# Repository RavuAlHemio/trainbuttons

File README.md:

# trainbuttons

Two boards providing buttons for controlling a train (simulator).

The buttons are provided by keyboard key switches (Cherry MX or compatible). The two boards are to be interconnected via a repurposed HDMI cable; the left board is then connected via USB-C to the computer.

The button layout is inspired by the results of the EUDDplus (European Driver's Desk plus) project and UIC 612. The icons are reconstructed from those in EN 16186-2. The buttons chosen are those supported, or expected to be supported, by the Zusi simulator.

The design does not include throttle or brake levers; potentiometer-based solutions are available from [Stillertec](https://fahrpult.com/).

The default firmware lets the device appear as a HID gamepad device with zero axes and 21 buttons. A debug pin header is provided on the board to allow installation of other firmware.

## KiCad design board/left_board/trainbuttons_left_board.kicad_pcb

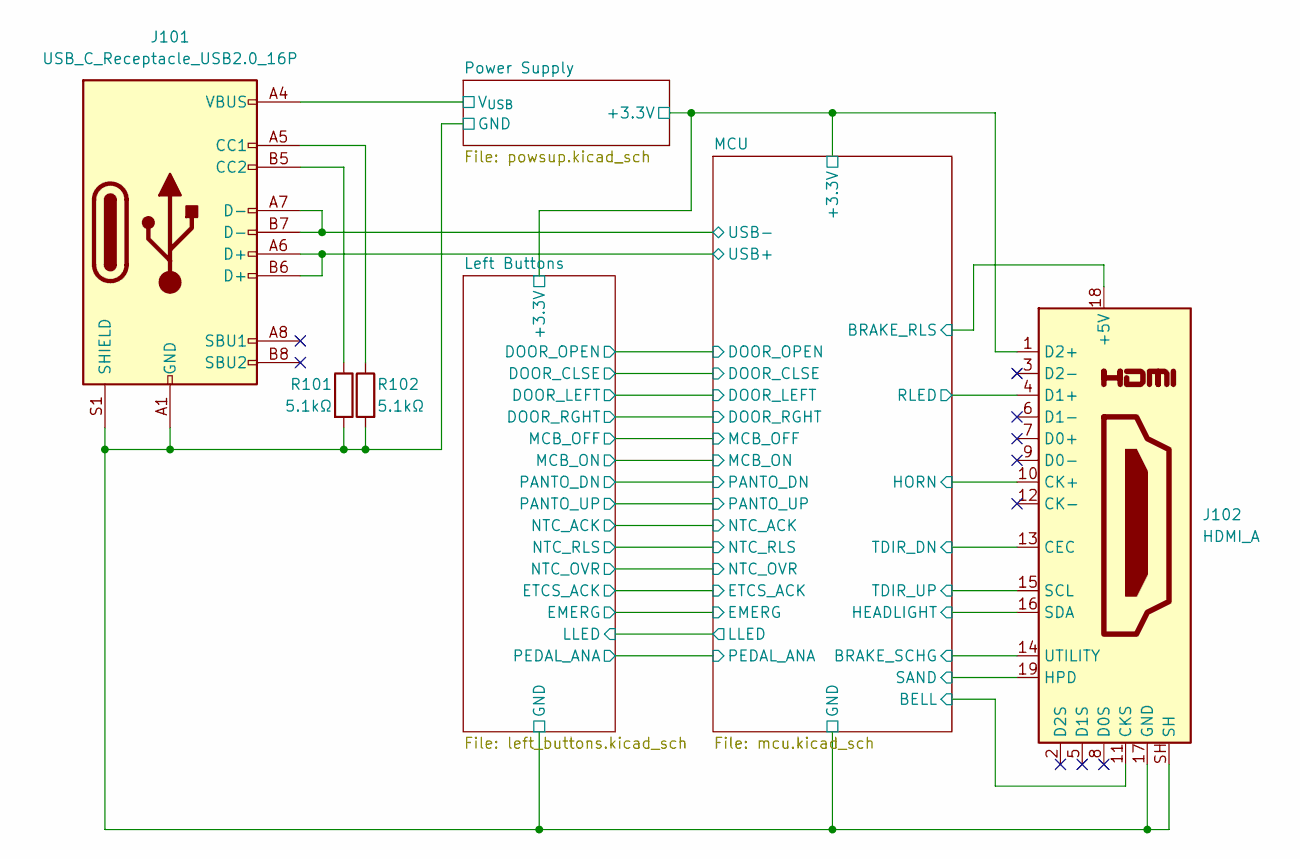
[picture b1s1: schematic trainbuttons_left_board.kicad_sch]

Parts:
J101: USB_C_Receptacle_USB2.0_16P; USB_C_Receptacle_G-Switch_GT-USB-7010ASV; LCSC C2988369
J102: HDMI_A; HDMI_A_Molex_208658-1001_Horizontal; LCSC C2858275
R101, R102: 5.1kΩ; R_0402_1005Metric; LCSC C25905

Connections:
/Left Buttons/+3.3V: J102.1 (D2+); also elsewhere on the board
/Left Buttons/GND: J101.A1 (GND), J101.A12 (GND), J101.B1 (GND), J101.B12 (GND), J101.S1 (SHIELD), J102.17 (GND), J102.SH, R101.2, R102.2; also elsewhere on the board
/MCU/BELL: J102.11 (CKS); also elsewhere on the board
/MCU/BRAKE_RLS: J102.18 (+5V); also elsewhere on the board
/MCU/BRAKE_SCHG: J102.14 (UTILITY); also elsewhere on the board
/MCU/HEADLIGHT: J102.16 (SDA); also elsewhere on the board
/MCU/HORN: J102.10 (CK+); also elsewhere on the board
/MCU/RLED: J102.4 (D1+); also elsewhere on the board
/MCU/SAND: J102.19 (HPD); also elsewhere on the board
/MCU/TDIR_DN: J102.13 (CEC); also elsewhere on the board
/MCU/TDIR_UP: J102.15 (SCL); also elsewhere on the board
/MCU/USB+: J101.A6 (D+), J101.B6 (D+); also elsewhere on the board
/MCU/USB-: J101.A7 (D-), J101.B7 (D-); also elsewhere on the board
/Power Supply/V_{USB}: J101.A4 (VBUS), J101.A9 (VBUS), J101.B4 (VBUS), J101.B9 (VBUS); also elsewhere on the board
unnamed: J101.A5 (CC1), R102.1
unnamed: J101.B5 (CC2), R101.1

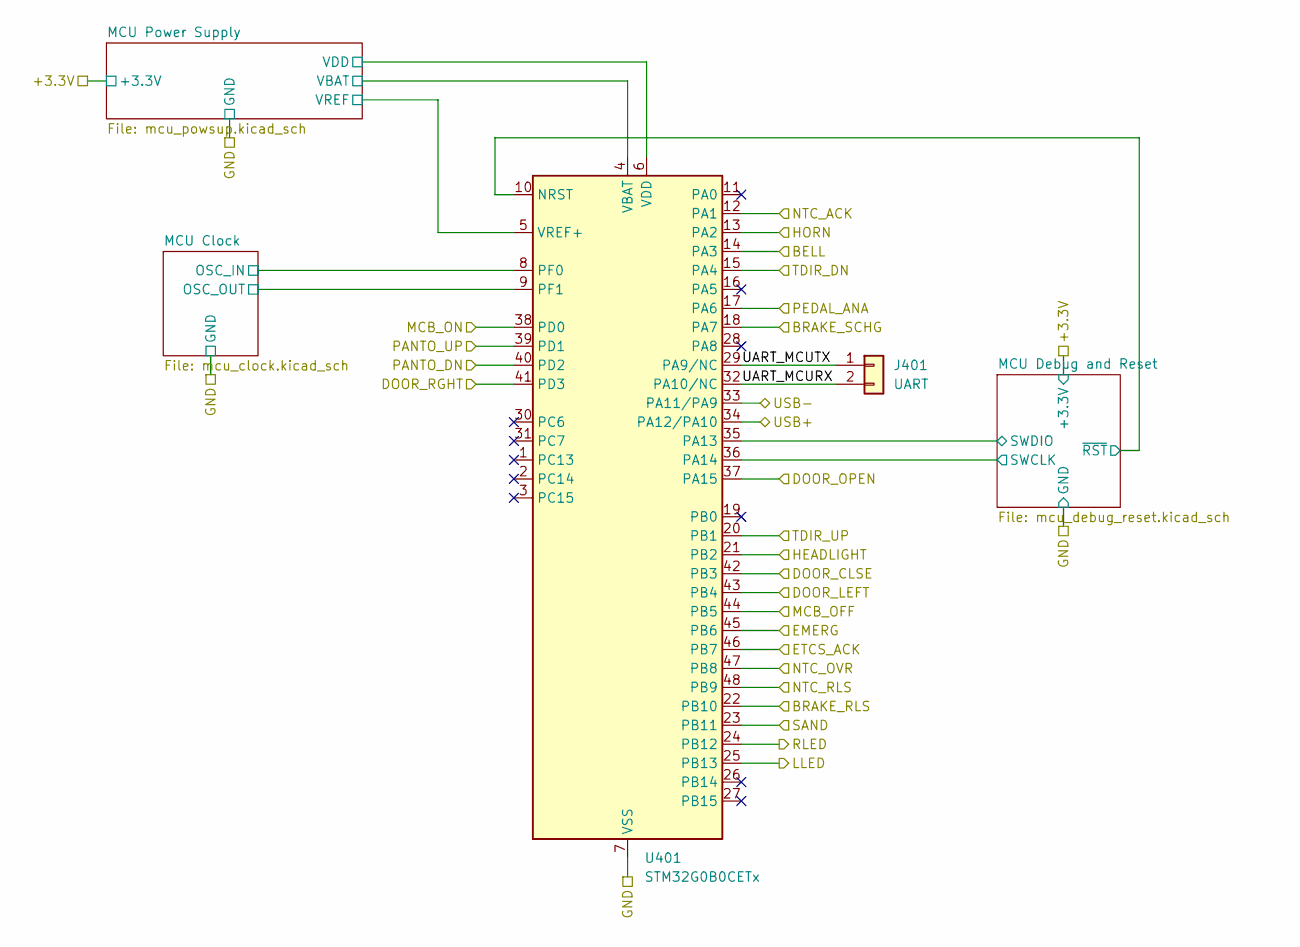
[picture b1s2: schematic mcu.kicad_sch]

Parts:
J401: UART; PinHeader_1x02_P2.54mm_Vertical_SMD_Pin1Left; LCSC C5160785
U401: STM32G0B0CETx; LQFP-48_7x7mm_P0.5mm; LCSC C2826978

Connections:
/Left Buttons/+3.3V: U401.4 (VBAT), U401.6 (VDD); also elsewhere on the board
/Left Buttons/DOOR_CLSE: U401.42 (PB3); also elsewhere on the board
/Left Buttons/DOOR_LEFT: U401.43 (PB4); also elsewhere on the board
/Left Buttons/DOOR_OPEN: U401.37 (PA15); also elsewhere on the board
/Left Buttons/DOOR_RGHT: U401.41 (PD3); also elsewhere on the board
/Left Buttons/EMERG: U401.45 (PB6); also elsewhere on the board
/Left Buttons/ETCS_ACK: U401.46 (PB7); also elsewhere on the board
/Left Buttons/GND: U401.7 (VSS); also elsewhere on the board
/Left Buttons/LLED: U401.25 (PB13); also elsewhere on the board
/Left Buttons/MCB_OFF: U401.44 (PB5); also elsewhere on the board
/Left Buttons/MCB_ON: U401.38 (PD0); also elsewhere on the board
/Left Buttons/NTC_ACK: U401.12 (PA1); also elsewhere on the board
/Left Buttons/NTC_OVR: U401.47 (PB8); also elsewhere on the board
/Left Buttons/NTC_RLS: U401.48 (PB9); also elsewhere on the board
/Left Buttons/PANTO_DN: U401.40 (PD2); also elsewhere on the board
/Left Buttons/PANTO_UP: U401.39 (PD1); also elsewhere on the board
/Left Buttons/PEDAL_ANA: U401.17 (PA6); also elsewhere on the board
/MCU/BELL: U401.14 (PA3); also elsewhere on the board
/MCU/BRAKE_RLS: U401.22 (PB10); also elsewhere on the board
/MCU/BRAKE_SCHG: U401.18 (PA7); also elsewhere on the board
/MCU/HEADLIGHT: U401.21 (PB2); also elsewhere on the board
/MCU/HORN: U401.13 (PA2); also elsewhere on the board
/MCU/MCU Clock/OSC_IN: U401.8 (PF0); also elsewhere on the board
/MCU/MCU Clock/OSC_OUT: U401.9 (PF1); also elsewhere on the board
/MCU/MCU Debug and Reset/SWCLK: U401.36 (PA14); also elsewhere on the board
/MCU/MCU Debug and Reset/SWDIO: U401.35 (PA13); also elsewhere on the board
/MCU/MCU Debug and Reset/~RST: U401.10 (NRST); also elsewhere on the board
/MCU/MCU Power Supply/VREF: U401.5 (VREF+); also elsewhere on the board
/MCU/RLED: U401.24 (PB12); also elsewhere on the board
/MCU/SAND: U401.23 (PB11); also elsewhere on the board
/MCU/TDIR_DN: U401.15 (PA4); also elsewhere on the board
/MCU/TDIR_UP: U401.20 (PB1); also elsewhere on the board
/MCU/UART_MCURX: J401.2, U401.32 (PA10/NC)
/MCU/UART_MCUTX: J401.1, U401.29 (PA9/NC)
/MCU/USB+: U401.34 (PA12/PA10); also elsewhere on the board
/MCU/USB-: U401.33 (PA11/PA9); also elsewhere on the board

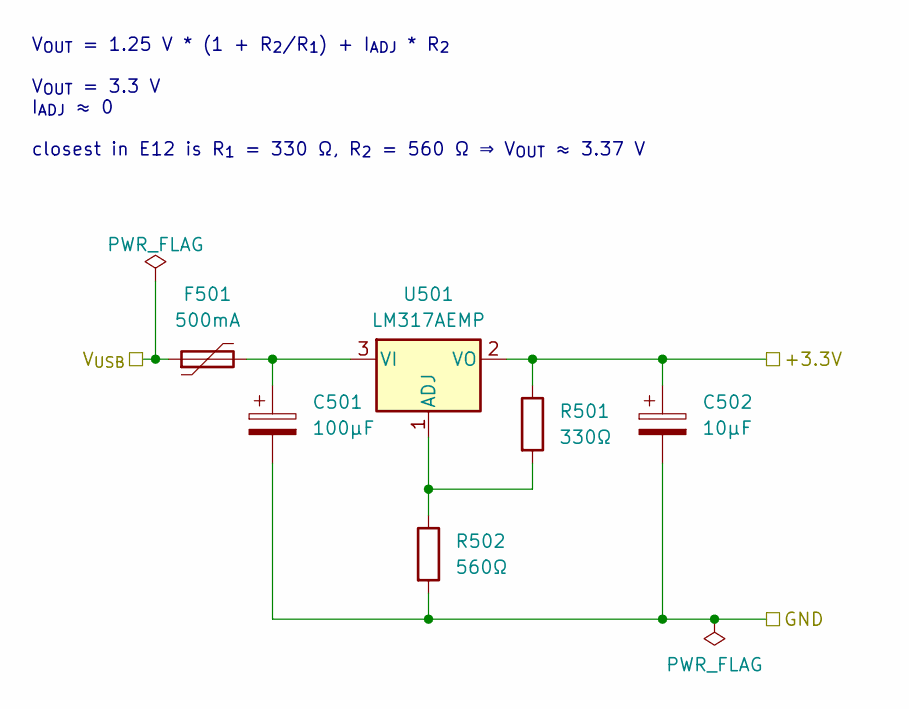
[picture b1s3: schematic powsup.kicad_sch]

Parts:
C501: 100µF; CP_EIA-3528-21_Kemet-B; LCSC C16133
C502: 10µF; CP_EIA-3216-18_Kemet-A; LCSC C7171
F501: 500mA; Fuse_0805_2012Metric; LCSC C2977522
R501: 330Ω; R_0603_1608Metric; LCSC C23138
R502: 560Ω; R_0603_1608Metric; LCSC C23204
U501: LM317AEMP; SOT-223-3_TabPin2; LCSC C33586

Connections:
/Left Buttons/+3.3V: C502.1, R501.1, U501.2 (VO); also elsewhere on the board
/Left Buttons/GND: C501.2, C502.2, R502.2; also elsewhere on the board
/Power Supply/V_{USB}: F501.1; also elsewhere on the board
unnamed: R501.2, R502.1, U501.1 (ADJ)
unnamed: C501.1, F501.2, U501.3 (VI)

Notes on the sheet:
V_{OUT} = 1.25 V * (1 + R_{2}/R_{1}) + I_{ADJ} * R_{2} V_{OUT} = 3.3 V I_{ADJ} ≈ 0 closest in E12 is R_{1} = 330 Ω, R_{2} = 560 Ω ⇒ V_{OUT} ≈ 3.37 V

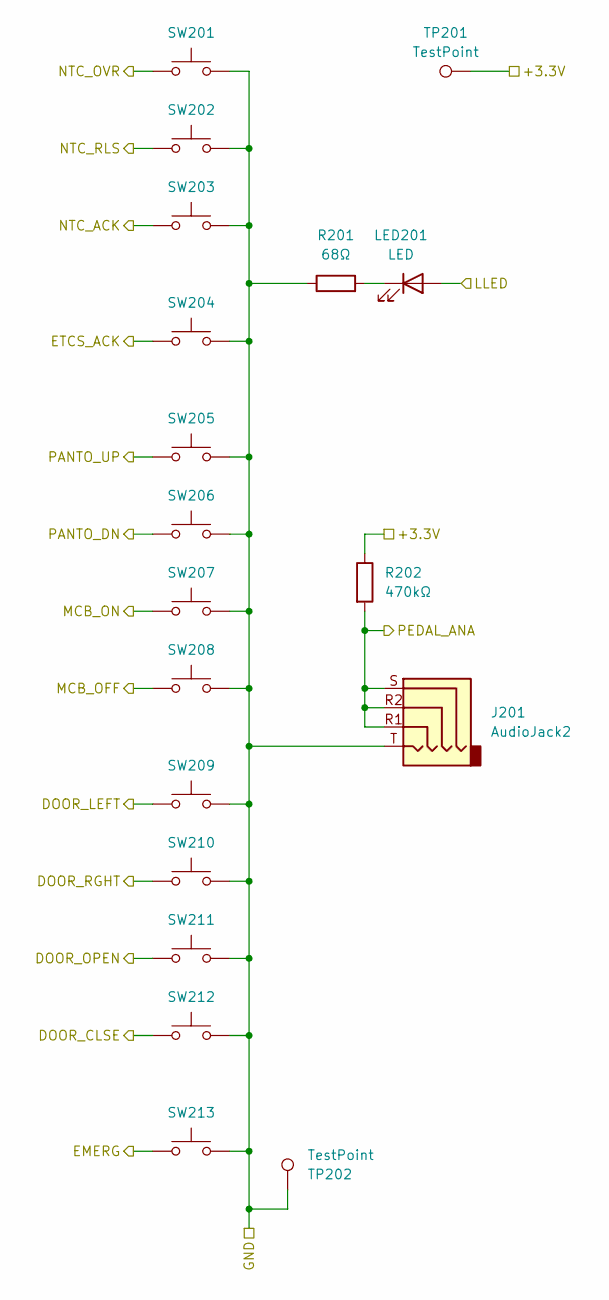
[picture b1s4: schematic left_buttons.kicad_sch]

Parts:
J201: AudioJack2; Jack_3.5mm_PJ320D_Horizontal; LCSC C431535
LED201: LED; LED_0805_2012Metric; LCSC C2296
R201: 68Ω; R_0805_2012Metric; LCSC C17802
R202: 470kΩ; R_0603_1608Metric; LCSC C23178
SW201, SW202, SW203, SW204, SW205, SW206, SW207, SW208, SW209, SW210, SW211, SW212, SW213: SW_Push; SW_Cherry_MX_1.00u_PCB
TP201, TP202: TestPoint; TestPoint_Pad_D1.0mm

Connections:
/Left Buttons/+3.3V: R202.1, TP201.1; also elsewhere on the board
/Left Buttons/DOOR_CLSE: SW212.1; also elsewhere on the board
/Left Buttons/DOOR_LEFT: SW209.1; also elsewhere on the board
/Left Buttons/DOOR_OPEN: SW211.1; also elsewhere on the board
/Left Buttons/DOOR_RGHT: SW210.1; also elsewhere on the board
/Left Buttons/EMERG: SW213.1; also elsewhere on the board
/Left Buttons/ETCS_ACK: SW204.1; also elsewhere on the board
/Left Buttons/GND: J201.T, R201.1, SW201.2, SW202.2, SW203.2, SW204.2, SW205.2, SW206.2, SW207.2, SW208.2, SW209.2, SW210.2, SW211.2, SW212.2, SW213.2, TP202.1; also elsewhere on the board
/Left Buttons/LLED: LED201.2 (A); also elsewhere on the board
/Left Buttons/MCB_OFF: SW208.1; also elsewhere on the board
/Left Buttons/MCB_ON: SW207.1; also elsewhere on the board
/Left Buttons/NTC_ACK: SW203.1; also elsewhere on the board
/Left Buttons/NTC_OVR: SW201.1; also elsewhere on the board
/Left Buttons/NTC_RLS: SW202.1; also elsewhere on the board
/Left Buttons/PANTO_DN: SW206.1; also elsewhere on the board
/Left Buttons/PANTO_UP: SW205.1; also elsewhere on the board
/Left Buttons/PEDAL_ANA: J201.R1, J201.R2, J201.S, R202.2; also elsewhere on the board
unnamed: LED201.1 (K), R201.2

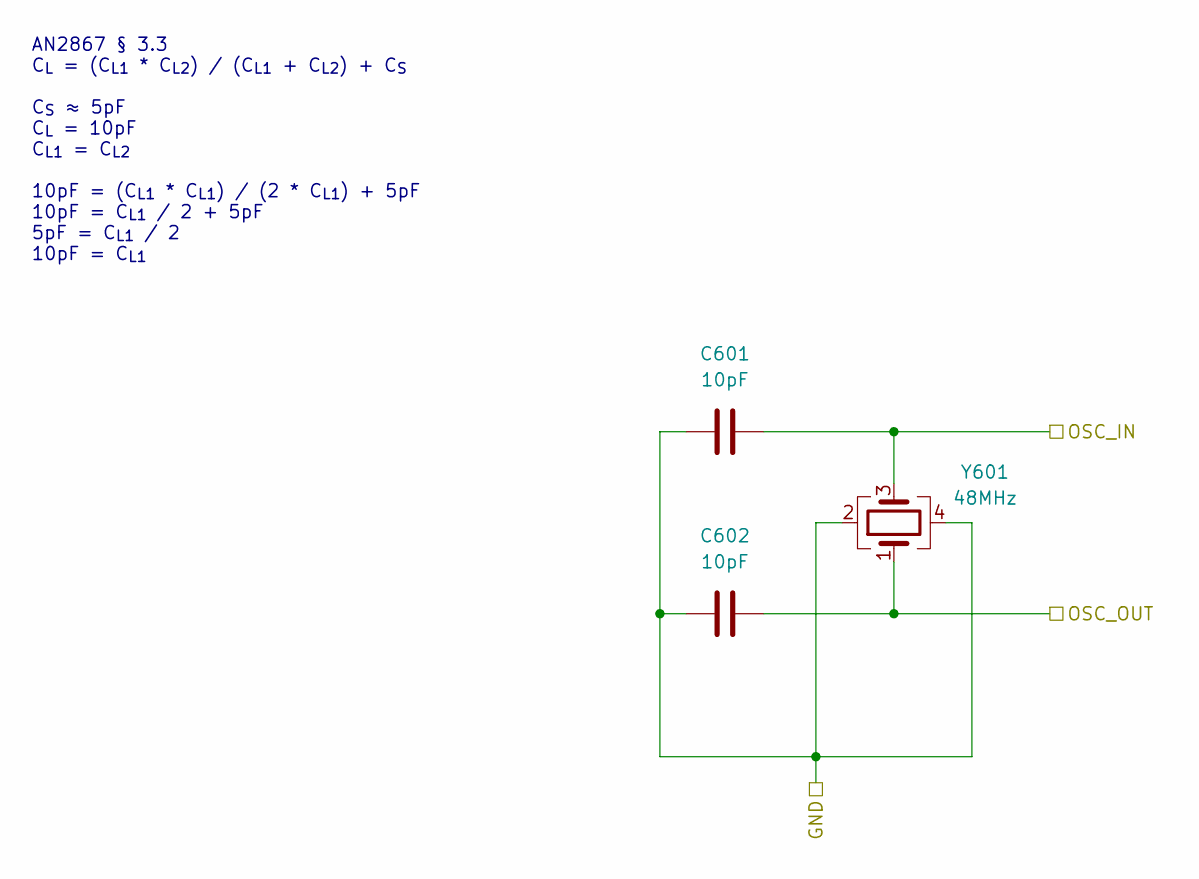
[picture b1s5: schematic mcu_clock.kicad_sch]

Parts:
C601, C602: 10pF; C_0402_1005Metric; LCSC C32949
Y601: 48MHz; Crystal_SMD_2016-4Pin_2.0x1.6mm; LCSC C648978

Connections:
/Left Buttons/GND: C601.1, C602.1, Y601.2, Y601.4; also elsewhere on the board
/MCU/MCU Clock/OSC_IN: C601.2, Y601.3; also elsewhere on the board
/MCU/MCU Clock/OSC_OUT: C602.2, Y601.1; also elsewhere on the board

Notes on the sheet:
AN2867 § 3.3 C_{L} = (C_{L1} * C_{L2}) / (C_{L1} + C_{L2}) + C_{S} C_{S} ≈ 5pF C_{L} = 10pF C_{L1} = C_{L2} 10pF = (C_{L1} * C_{L1}) / (2 * C_{L1}) + 5pF 10pF = C_{L1} / 2 + 5pF 5pF = C_{L1} / 2 10pF = C_{L1}

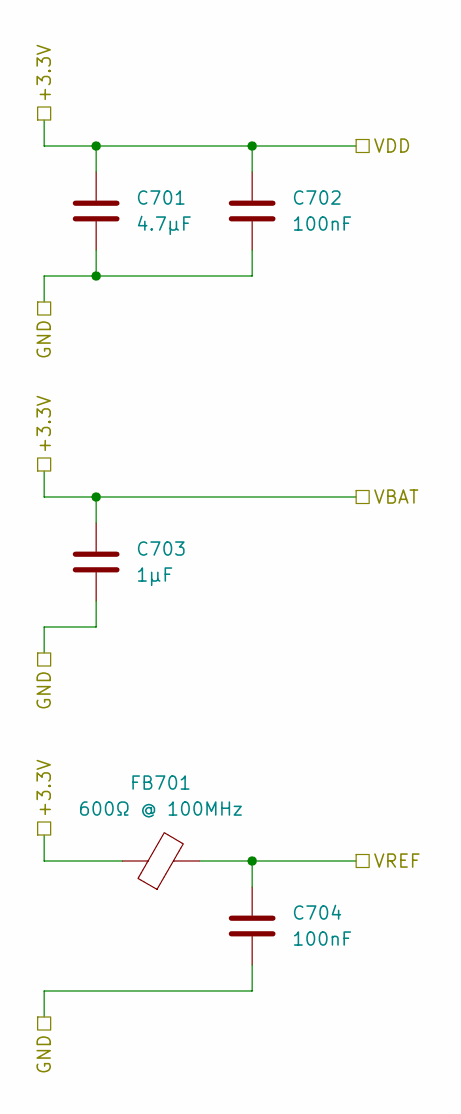
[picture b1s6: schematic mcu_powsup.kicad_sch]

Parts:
C701: 4.7μF; C_0402_1005Metric; LCSC C23733
C702, C704: 100nF; C_0402_1005Metric; LCSC C307331
C703: 1μF; C_0402_1005Metric; LCSC C52923
FB701: 600Ω @ 100MHz; L_0402_1005Metric; LCSC C560060

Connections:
/Left Buttons/+3.3V: C701.1, C702.1, C703.1, FB701.1; also elsewhere on the board
/Left Buttons/GND: C701.2, C702.2, C703.2, C704.2; also elsewhere on the board
/MCU/MCU Power Supply/VREF: C704.1, FB701.2; also elsewhere on the board

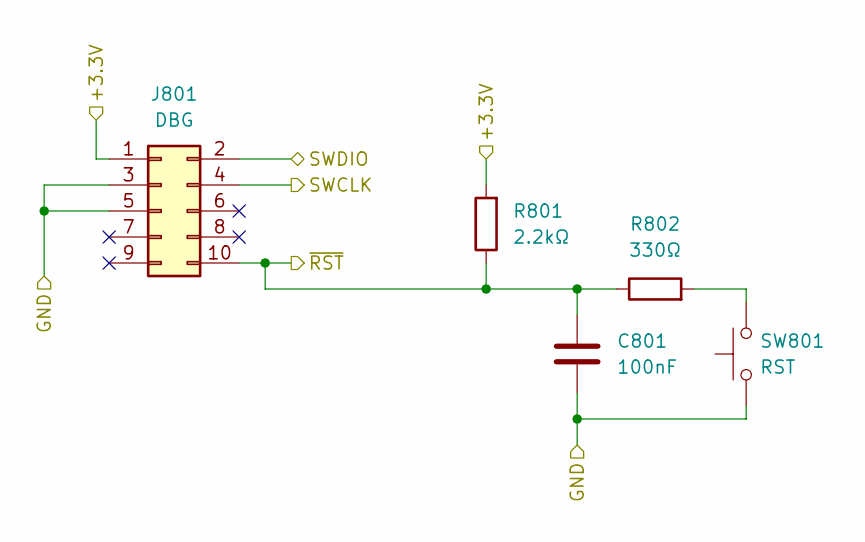
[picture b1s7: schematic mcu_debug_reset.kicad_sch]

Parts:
C801: 100nF; C_0402_1005Metric; LCSC C307331
J801: DBG; PinHeader_2x05_P1.27mm_Vertical_SMD; LCSC C5250218
R801: 2.2kΩ; R_0402_1005Metric; LCSC C25879
R802: 330Ω; R_0402_1005Metric; LCSC C25104
SW801: RST; SW_Push_1P1T_XKB_TS-1187A; LCSC C318884

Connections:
/Left Buttons/+3.3V: J801.1, R801.2; also elsewhere on the board
/Left Buttons/GND: C801.1, J801.3, J801.5, SW801.1; also elsewhere on the board
/MCU/MCU Debug and Reset/SWCLK: J801.4; also elsewhere on the board
/MCU/MCU Debug and Reset/SWDIO: J801.2; also elsewhere on the board
/MCU/MCU Debug and Reset/~RST: C801.2, J801.10, R801.1, R802.1; also elsewhere on the board
unnamed: R802.2, SW801.2

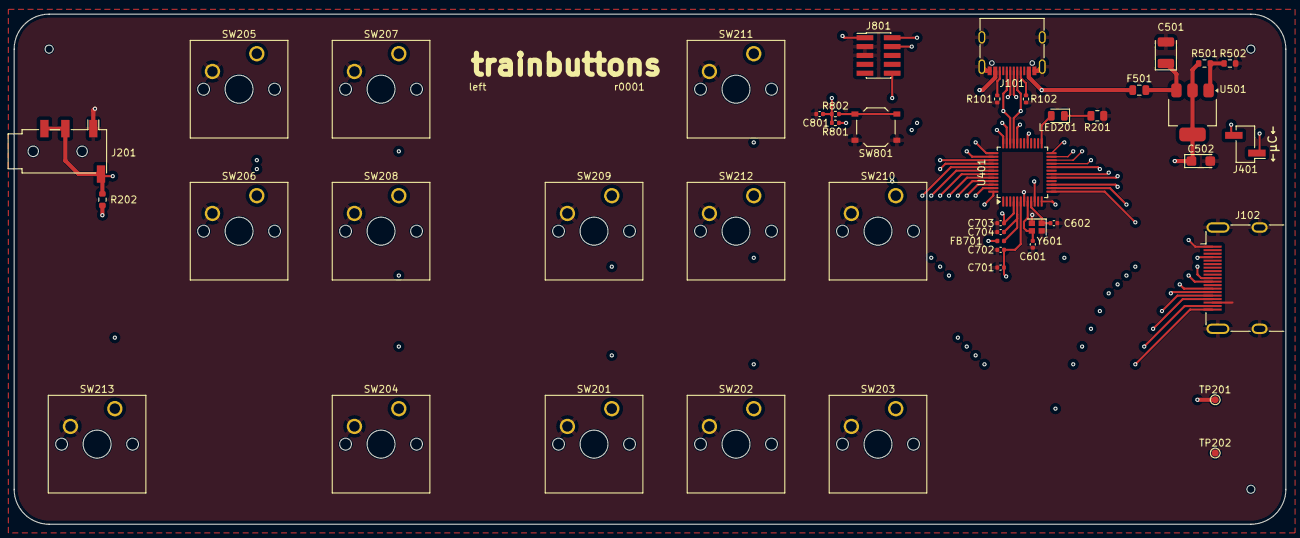
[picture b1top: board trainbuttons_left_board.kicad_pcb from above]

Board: 4 copper layers, 182.0 x 73.0 mm, 44 parts (0 on the bottom side), 43 nets.

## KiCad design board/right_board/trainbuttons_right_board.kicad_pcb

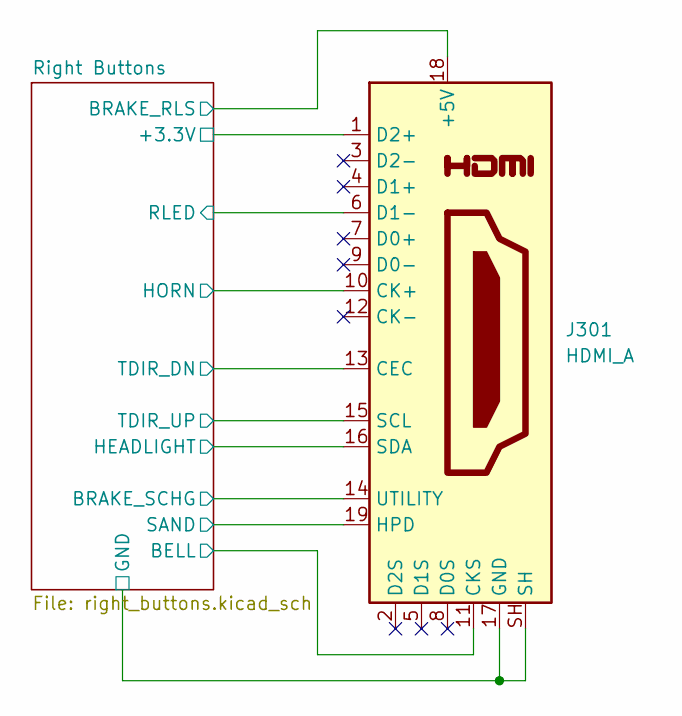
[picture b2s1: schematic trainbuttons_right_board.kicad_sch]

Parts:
J301: HDMI_A; HDMI_A_Molex_208658-1001_Horizontal; LCSC C2858275

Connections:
/Right Buttons/+3.3V: J301.1 (D2+); also elsewhere on the board
/Right Buttons/BELL: J301.11 (CKS); also elsewhere on the board
/Right Buttons/BRAKE_RLS: J301.18 (+5V); also elsewhere on the board
/Right Buttons/BRAKE_SCHG: J301.14 (UTILITY); also elsewhere on the board
/Right Buttons/GND: J301.17 (GND), J301.SH; also elsewhere on the board
/Right Buttons/HEADLIGHT: J301.16 (SDA); also elsewhere on the board
/Right Buttons/HORN: J301.10 (CK+); also elsewhere on the board
/Right Buttons/RLED: J301.6 (D1-); also elsewhere on the board
/Right Buttons/SAND: J301.19 (HPD); also elsewhere on the board
/Right Buttons/TDIR_DN: J301.13 (CEC); also elsewhere on the board
/Right Buttons/TDIR_UP: J301.15 (SCL); also elsewhere on the board

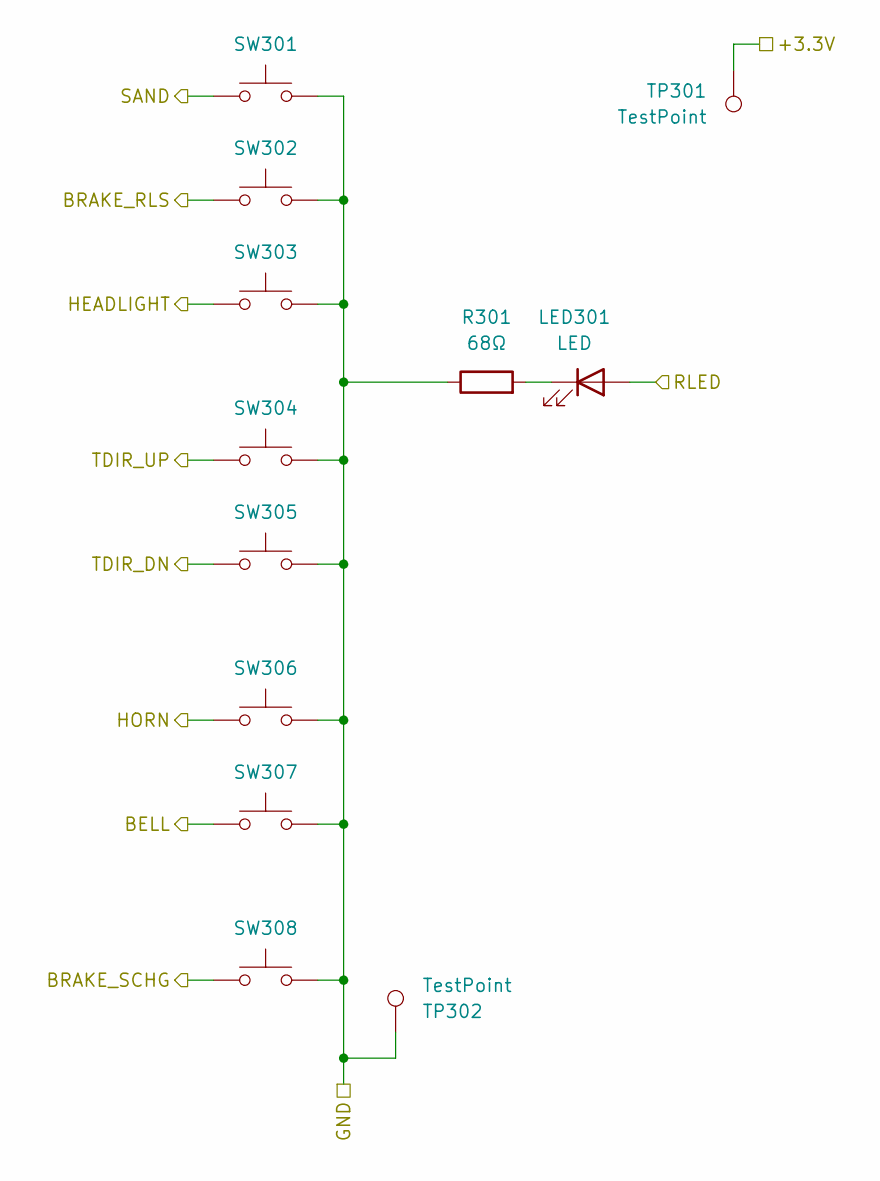
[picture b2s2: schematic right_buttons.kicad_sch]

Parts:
LED301: LED; LED_0805_2012Metric; LCSC C2296
R301: 68Ω; R_0805_2012Metric; LCSC C17802
SW301, SW302, SW303, SW304, SW305, SW306, SW307, SW308: SW_Push; SW_Cherry_MX_1.00u_PCB
TP301, TP302: TestPoint; TestPoint_Pad_D1.0mm

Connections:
/Right Buttons/+3.3V: TP301.1; also elsewhere on the board
/Right Buttons/BELL: SW307.1; also elsewhere on the board
/Right Buttons/BRAKE_RLS: SW302.1; also elsewhere on the board
/Right Buttons/BRAKE_SCHG: SW308.1; also elsewhere on the board
/Right Buttons/GND: R301.1, SW301.2, SW302.2, SW303.2, SW304.2, SW305.2, SW306.2, SW307.2, SW308.2, TP302.1; also elsewhere on the board
/Right Buttons/HEADLIGHT: SW303.1; also elsewhere on the board
/Right Buttons/HORN: SW306.1; also elsewhere on the board
/Right Buttons/RLED: LED301.2 (A); also elsewhere on the board
/Right Buttons/SAND: SW301.1; also elsewhere on the board
/Right Buttons/TDIR_DN: SW305.1; also elsewhere on the board
/Right Buttons/TDIR_UP: SW304.1; also elsewhere on the board
unnamed: LED301.1 (K), R301.2

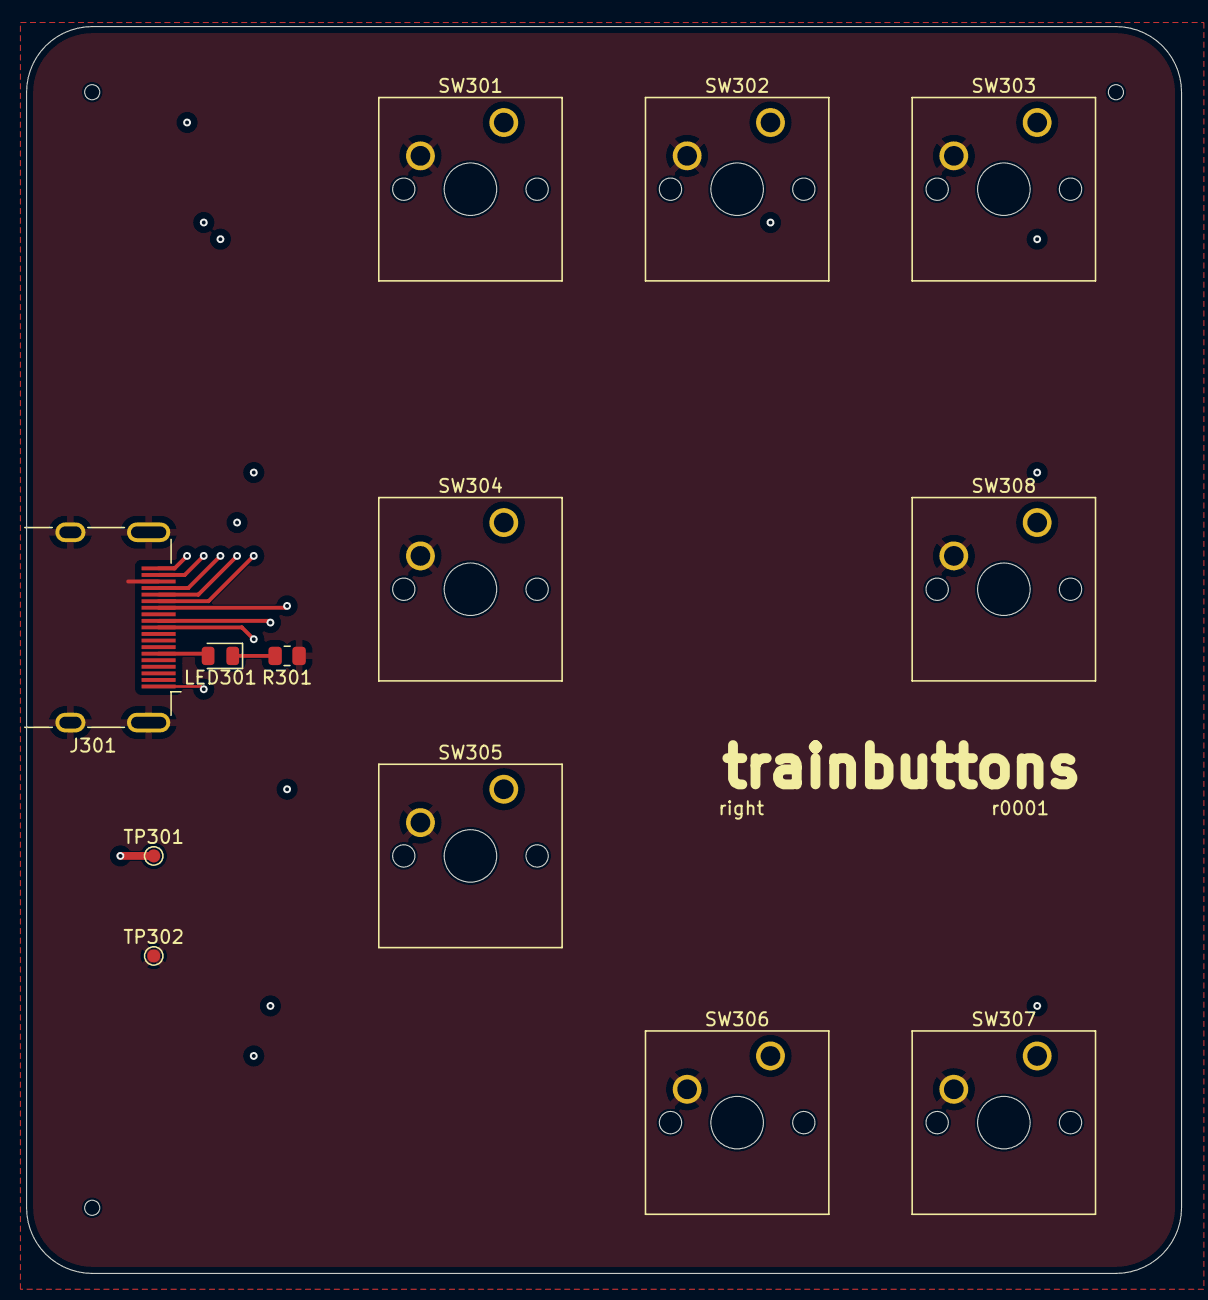
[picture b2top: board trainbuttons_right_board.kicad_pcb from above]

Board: 4 copper layers, 88.0 x 95.0 mm, 13 parts (0 on the bottom side), 12 nets.

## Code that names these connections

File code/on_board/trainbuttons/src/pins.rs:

//! Interfacing with general-purpose input/output (GPIO) pins.


use bitmacros::{bit_mask, extract_bits};
use stm32g0b0::Peripherals;


pub(crate) fn enable_peripheral_clocks(peripherals: &Peripherals) {
    // send clock to GPIOA, GPIOB and GPIOD
    peripherals.rcc.iopenr().modify(|_, w| w
        .gpioaen().set_bit()
        .gpioben().set_bit()
        .gpioden().set_bit()
    );
}

pub(crate) fn start_reset(peripherals: &Peripherals) {
    // reset GPIOA, GPIOB and GPIOD
    peripherals.rcc.ioprstr().modify(|_, w| w
        .gpioarst().set_bit()
        .gpiobrst().set_bit()
        .gpiodrst().set_bit()
    );
}

pub(crate) fn stop_reset(peripherals: &Peripherals) {
    // disable reset of GPIOA, GPIOB and GPIOD
    peripherals.rcc.ioprstr().modify(|_, w| w
        .gpioarst().clear_bit()
        .gpiobrst().clear_bit()
        .gpiodrst().clear_bit()
    );
}

pub(crate) fn set_up(peripherals: &Peripherals) {
    // set up buttons (digital input, pull up)
    // and LEDs (output, push-pull)
    peripherals.gpioa.moder().modify(|_, w| w
        .moder1().input()
        .moder2().input()
        .moder3().input()
        .moder4().input()
        .moder7().input()
        .moder15().input()
    );
    peripherals.gpiob.moder().modify(|_, w| w
        .moder1().input()
        .moder2().input()
        .moder3().input()
        .moder4().input()
        .moder5().input()
        .moder6().input()
        .moder7().input()
        .moder8().input()
        .moder9().input()
        .moder10().input()
        .moder11().input()
        .moder12().general_purpose_output()
        .moder13().general_purpose_output()
    );
    peripherals.gpiod.moder().modify(|_, w| w
        .moder0().input()
        .moder1().input()
        .moder2().input()
        .moder3().input()
    );
    peripherals.gpioa.pupdr().modify(|_, w| w
        .pupdr1().pull_up()
        .pupdr2().pull_up()
        .pupdr3().pull_up()
        .pupdr4().pull_up()
        .pupdr7().pull_up()
        .pupdr15().pull_up()
    );
    peripherals.gpiob.pupdr().modify(|_, w| w
        .pupdr1().pull_up()
        .pupdr2().pull_up()
        .pupdr3().pull_up()
        .pupdr4().pull_up()
        .pupdr5().pull_up()
        .pupdr6().pull_up()
        .pupdr7().pull_up()
        .pupdr8().pull_up()
        .pupdr9().pull_up()
        .pupdr10().pull_up()
        .pupdr11().pull_up()
    );
    peripherals.gpiod.pupdr().modify(|_, w| w
        .pupdr0().pull_up()
        .pupdr1().pull_up()
        .pupdr2().pull_up()
        .pupdr3().pull_up()
    );
    peripherals.gpiob.otyper().modify(|_, w| w
        .ot12().push_pull()
        .ot13().push_pull()
    );
}

pub(crate) fn read_button_states(peripherals: &Peripherals) -> u32 {
    // buttons are:
    // PA1-PA4, PA7, PA15 (6 bits)
    // PB1-PB11 (11 bits)
    // [PB12 and PB13 are LEDs]
    // PD0-PD3 (4 bits)
    let pa_bits = peripherals.gpioa.idr().read().bits();
    let pa_button_states: u32 =
        (extract_bits!(pa_bits, 1, 4) ^ bit_mask!(0, 4))
        | ((extract_bits!(pa_bits, 7, 1) ^ bit_mask!(0, 1)) << 4)
        | ((extract_bits!(pa_bits, 15, 1) ^ bit_mask!(0, 1)) << 5)
    ;
    let pb_bits = peripherals.gpiob.idr().read().bits();
    let pb_button_states: u32 =
        extract_bits!(pb_bits, 1, 11) ^ bit_mask!(0, 11)
    ;
    let pd_bits = peripherals.gpiod.idr().read().bits();
    let pd_button_states: u32 =
        extract_bits!(pd_bits, 0, 4) ^ bit_mask!(0, 4)
    ;

    // fill up from the least significant bit
    // 000D DDDB BBBB BBBB BBAA AAAA
    let all_button_states =
        pa_button_states
        | (pb_button_states << 6)
        | (pd_button_states << (6 + 11))
    ;
    all_button_states
}

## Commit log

2024-03-31 initial commit (WIP board)
2024-03-31 add initial code (autogenerated stm32g0b0)
2024-03-31 add project scaffolding for executable
2024-03-31 initial clock setup
2024-04-21 split board into left and right
2024-04-22 boards: add JLCPCB mounting holes
2024-04-22 initial USB code
2024-04-23 add button layout SVG
2024-04-23 button_layout: add standardized icons, start tracing them
2024-04-24 button_layout: trace more button icons
2024-04-24 button_layout: finish tracing icons
2024-08-04 schematics: trailing newlines
2024-08-04 left board: fix cap: 4.7nF -> 4.7µF
2024-08-04 board: PCB updates
2024-08-04 USB interrupt is 8
    this has been confirmed by ST in case 00202361
2024-08-04 increase GPIO awesomeness
2024-08-04 stm32g0b0: add USB RAM1
2024-08-04 stm32g0b0: re-export cortex_m_rt::interrupt
2024-08-04 GPIO setup, initial USB setup
2024-08-04 build scripts
2024-08-04 ignore tb.bin (build artifact)
2024-08-04 add individual keycap graphics
2024-08-05 stm32g0b0: regenerate using svd2rust 0.33.4
2024-08-05 stm32g0b0: mark some USB_RAM registers as safe
2024-08-05 further USB prep work
2024-08-05 stm32g0b0: USB quality-of-life improvements
2024-08-05 usb: initial buffer setup, hopefully
2024-08-06 stm32g0b0: USB endpoint registers as array
2024-08-06 some more USB
2024-08-08 usb: try statrx instead
2024-08-08 usb: fix buffer calculation
2024-08-09 stm32g0b0 usb: CHEPR -> CHEPNR
    optimally, the registers would be named CHEP0R, CHEP1R etc., but that doesn't work syntactically
    call them CHEPNR because that's a string that can be found in the relevant manuals
2024-08-09 stm32g0b0: make usb.daddr.add settable to any value
2024-08-09 move more usb stuff around, still doesn't work
2024-08-11 add code for debugging
2024-08-13 they lied to me
    USBSEL documentation is wrong. ST case 00212654 is open.
2024-08-13 get debug info in release builds too
2024-08-13 stm32g0b0: more enumerated values -- we like our creature comforts
2024-08-13 stm32g0b0: make some USB_CHEPnR fields readable too
    their bits are "write 1 to toggle", so reading them is necessary when
    wanting to set them to a specific value
2024-08-13 clock: slow down flash, disable PLL, pass to peripherals
2024-08-13 usb: more work
2024-08-15 move USB clock activation from clock to usb
2024-08-15 usb: reduce memory usage to two endpoints (four buffers)
    we will only have endpoint 0 (control) and 1 (HID)
2024-08-15 usb: get_*_buf: make more general to obtain the buffer of any endpoint
2024-08-15 usb: no more blinky when interrupt is hit
2024-08-17 stm32g0b0: add USART creature comforts
2024-08-17 implement UART
2024-08-17 left: replace UART pin header
    choose a 2.54mm variant that can be mounted easily
2024-08-17 left: add no-connects to MCU
2024-08-17 right: add revision text
2024-08-19 uart: also configure GPIO
2024-08-19 uart: hex dumping
2024-08-19 usb: I guess SYSCFG.ITLINE8.USB is not set (erratum?)
2024-08-19 usb: take USB interrupt handlers from HAL code
2024-08-19 usb: correctly set smaller buffer sizes too
2024-08-19 usb: WIP: CHEPnR modifier
    the USB_CHEPnR register is annoying because some of its fields are standard
    "write to set", some are "write zero to reset" and some are "write one to
    toggle"
2024-08-19 main: greet the world via UART
2024-08-19 usb: this will become a larger module
2024-08-19 usb: finish, and use, chepnr magic
2024-08-19 usb: remove unused use
2024-08-25 it's slowly starting to do something
    slowly
2024-08-25 stm32g0b0: dimIncrement is in bytes, not bits
2024-08-25 code: make it work
2024-09-10 add README
2024-09-10 release under CC0
2024-10-24 group "enable clock", "start reset" and "stop reset" per peripheral
    this makes it more straightforward to light up new peripherals later on
2024-10-24 move button state reading to the pins module
2024-10-24 stm32g0b0: ADC.CFGR2.CKMODE option beautification
2024-10-24 stm32g0b0: ADC.CFGR1.CHSELRMOD option beautification
2024-10-24 stm32g0b0: ADC.CFGR1.SCANDIR option beautification
2024-10-24 stm32g0b0: merge DMAx.CPARx register definitions
2024-10-24 stm32g0b0: remove DMA_ prefix from registers of DMA peripheral
2024-10-24 stm32g0b0: merge DMAx.CMARx register definitions
2024-10-24 stm32g0b0: make DMAx.CPARx.PA settable to direct values
2024-10-24 stm32g0b0: merge DMAx.CNDTRx register definitions
2024-10-24 stm32g0b0: make DMAx.CMARx.MA settable to direct values
2024-10-24 stm32g0b0: make DMAx.CNDTRx.NDT settable to direct values
2024-10-24 stm32g0b0: merge DMAx.CCRx register definitions
2024-10-24 stm32g0b0: DMAx.CCRx.DIR option beautification
2024-10-24 stm32g0b0: DMAx.CCRx.PL option beautification
2024-10-24 stm32g0b0: DMAx.CCRx.(PSIZE|MSIZE) option beautification
2024-10-24 stm32g0b0: merge DMAMUX.(CxCR|RGxCR) register definitions
2024-10-24 stm32g0b0: remove DMAMUX_ prefix from registers of DMAMUX peripheral
2024-10-24 stm32g0b0: widen DMAMUX.CxCR.DMAREQ_ID to 7 bits, add options
2024-10-24 stm32g0b0: ADC.CFGR1.EXTEN option beautification
2024-10-24 stm32g0b0: ADC.CFGR1.RES option beautification
2024-10-24 stm32g0b0: ADC.CFGR1.DMACFG option beautification
2024-10-24 stm32g0b0: ADC.CFGR1.ALIGN option beautification
2024-10-24 add support for pedal
    the pedal is mostly envisioned as a secondary dead man's switch input, but
    to enable flexible usage, it is wired up to the µC's ADC and supplies
    12-bit values for the X axis
    things will be set up to cooperate with a Brother-compatible sewing machine
    pedal because that's what I have lying around -- those that connect using a
    3.5mm TS phone connector, nothing even close to mains voltage
2024-10-24 stm32g0b0: remove ADC_ prefix from registers of ADC peripheral
2024-10-25 fix HID data alignment
2024-10-25 left board: pullup resistor for pedal
